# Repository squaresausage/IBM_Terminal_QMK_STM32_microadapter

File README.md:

# IBM_Terminal_QMK_STM32_microadapter

My attempt to design a very small and very cheap USB converter for IBM Model M terminal keyboards.

Intended to fit in between the pins of a 5 pin DIN 270° female connector, with a PCB edge USB A connector.

V0.2 now should actually match the pins of a DIN connector. Make sure to use the updated version of the keyboard config with the latest pinout for the F042.

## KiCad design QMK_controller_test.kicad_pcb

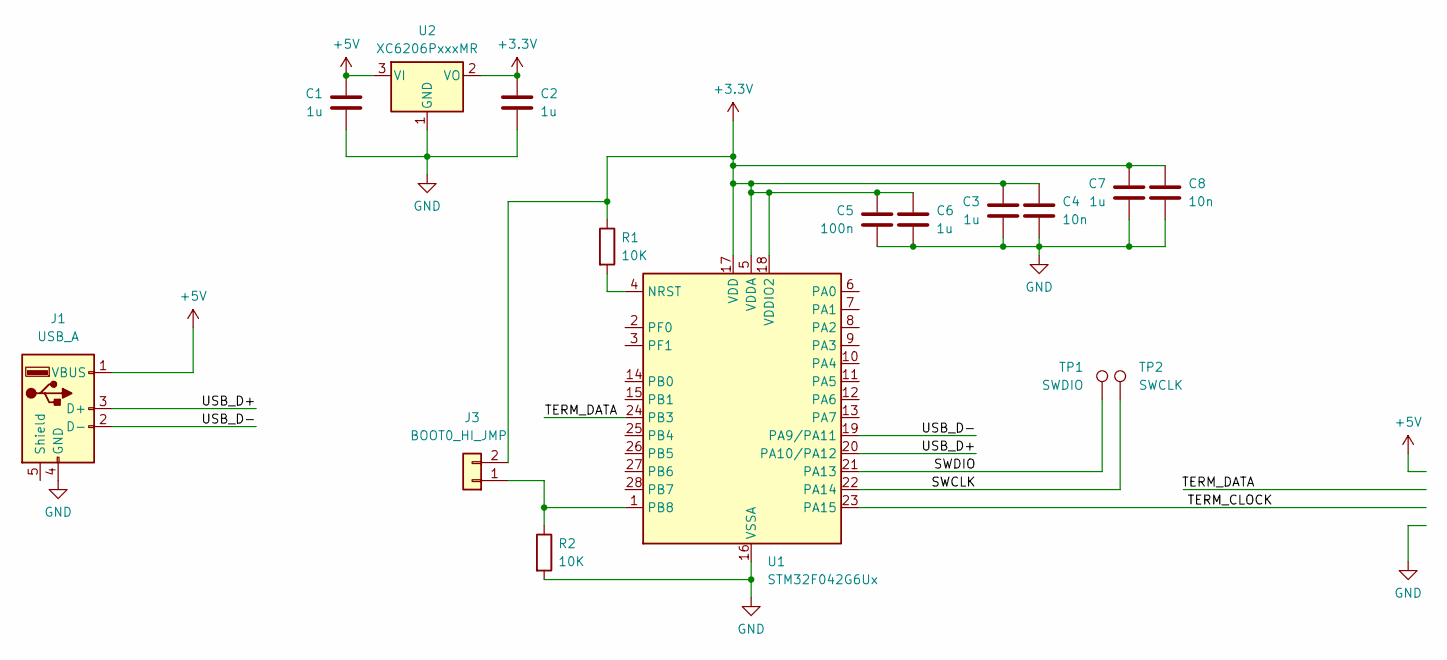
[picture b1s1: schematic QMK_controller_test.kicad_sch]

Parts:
C1, C2, C3, C6, C7: 1u; C_0402_1005Metric; LCSC C52923
C4, C8: 10n; C_0402_1005Metric; LCSC C15195
C5: 100n; C_0402_1005Metric; LCSC C1525
J1: USB_A; usb-PCB
J3: BOOT0_HI_JMP; PinHeader_1x02_P1.00mm_Vertical
R1, R2: 10K; R_0402_1005Metric; LCSC C25744
TP1: SWDIO; TestPoint_Pad_D1.0mm
TP2: SWCLK; TestPoint_Pad_D1.0mm
U1: STM32F042G6Ux; QFN-28_4x4mm_P0.5mm; LCSC C961597
U2: XC6206PxxxMR; SOT-23-3; LCSC C5446

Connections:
+3.3V: C2.1, C3.1, C4.1, C5.1, C6.1, C7.1, C8.1, J3.2, R1.1, U1.5 (VDDA), U1.17 (VDD), U1.18 (VDDIO2), U2.2 (VO)
+5V: C1.1, J1.1 (VBUS), U2.3 (VI)
/SWCLK: TP2.1, U1.22 (PA14)
/SWDIO: TP1.1, U1.21 (PA13)
/TERM_CLOCK: U1.23 (PA15)
/TERM_DATA: U1.24 (PB3)
/USB_D+: J1.3 (D+), U1.20 (PA10/PA12)
/USB_D-: J1.2 (D-), U1.19 (PA9/PA11)
GND: C1.2, C2.2, C3.2, C4.2, C5.2, C6.2, C7.2, C8.2, J1.4 (GND), R2.2, U1.16 (VSSA), U2.1 (GND)
unnamed: J3.1, R2.1, U1.1 (PB8)
unnamed: R1.2, U1.4 (NRST)

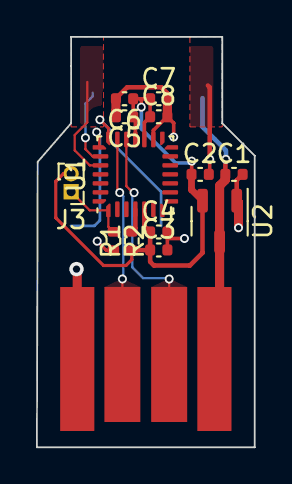
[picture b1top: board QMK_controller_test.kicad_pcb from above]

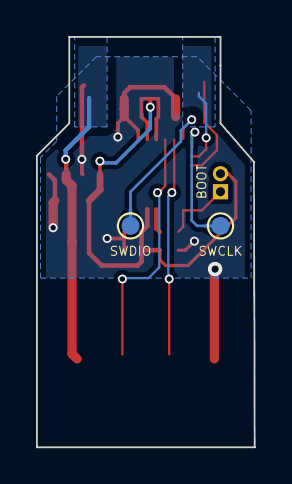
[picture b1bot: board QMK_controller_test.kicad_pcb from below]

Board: 2 copper layers, 12.1 x 22.8 mm, 16 parts (2 on the bottom side), 9 nets.

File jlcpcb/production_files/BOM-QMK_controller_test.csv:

Comment,Designator,Footprint,LCSC
10n,"C4,C8",C_0402_1005Metric,C15195
100n,C5,C_0402_1005Metric,C1525
10K,"R1,R2",R_0402_1005Metric,C25744
1u,"C1,C2,C3,C6,C7",C_0402_1005Metric,C52923
XC6206PxxxMR,U2,SOT-23-3,C5446
STM32F042G6Ux,U1,QFN-28_4x4mm_P0.5mm,C961597

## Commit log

2025-06-09 Init Commit
2025-06-09 added to the README
2025-06-09 V0.2 - Fixed broken DIN 5 pinout. Fixed SWD conflict pinout (PB3 - DATA, PA15 - CLOCK). Also added SWD testpoints.
2025-06-09 Updated readme to reflect V0.2 changes
